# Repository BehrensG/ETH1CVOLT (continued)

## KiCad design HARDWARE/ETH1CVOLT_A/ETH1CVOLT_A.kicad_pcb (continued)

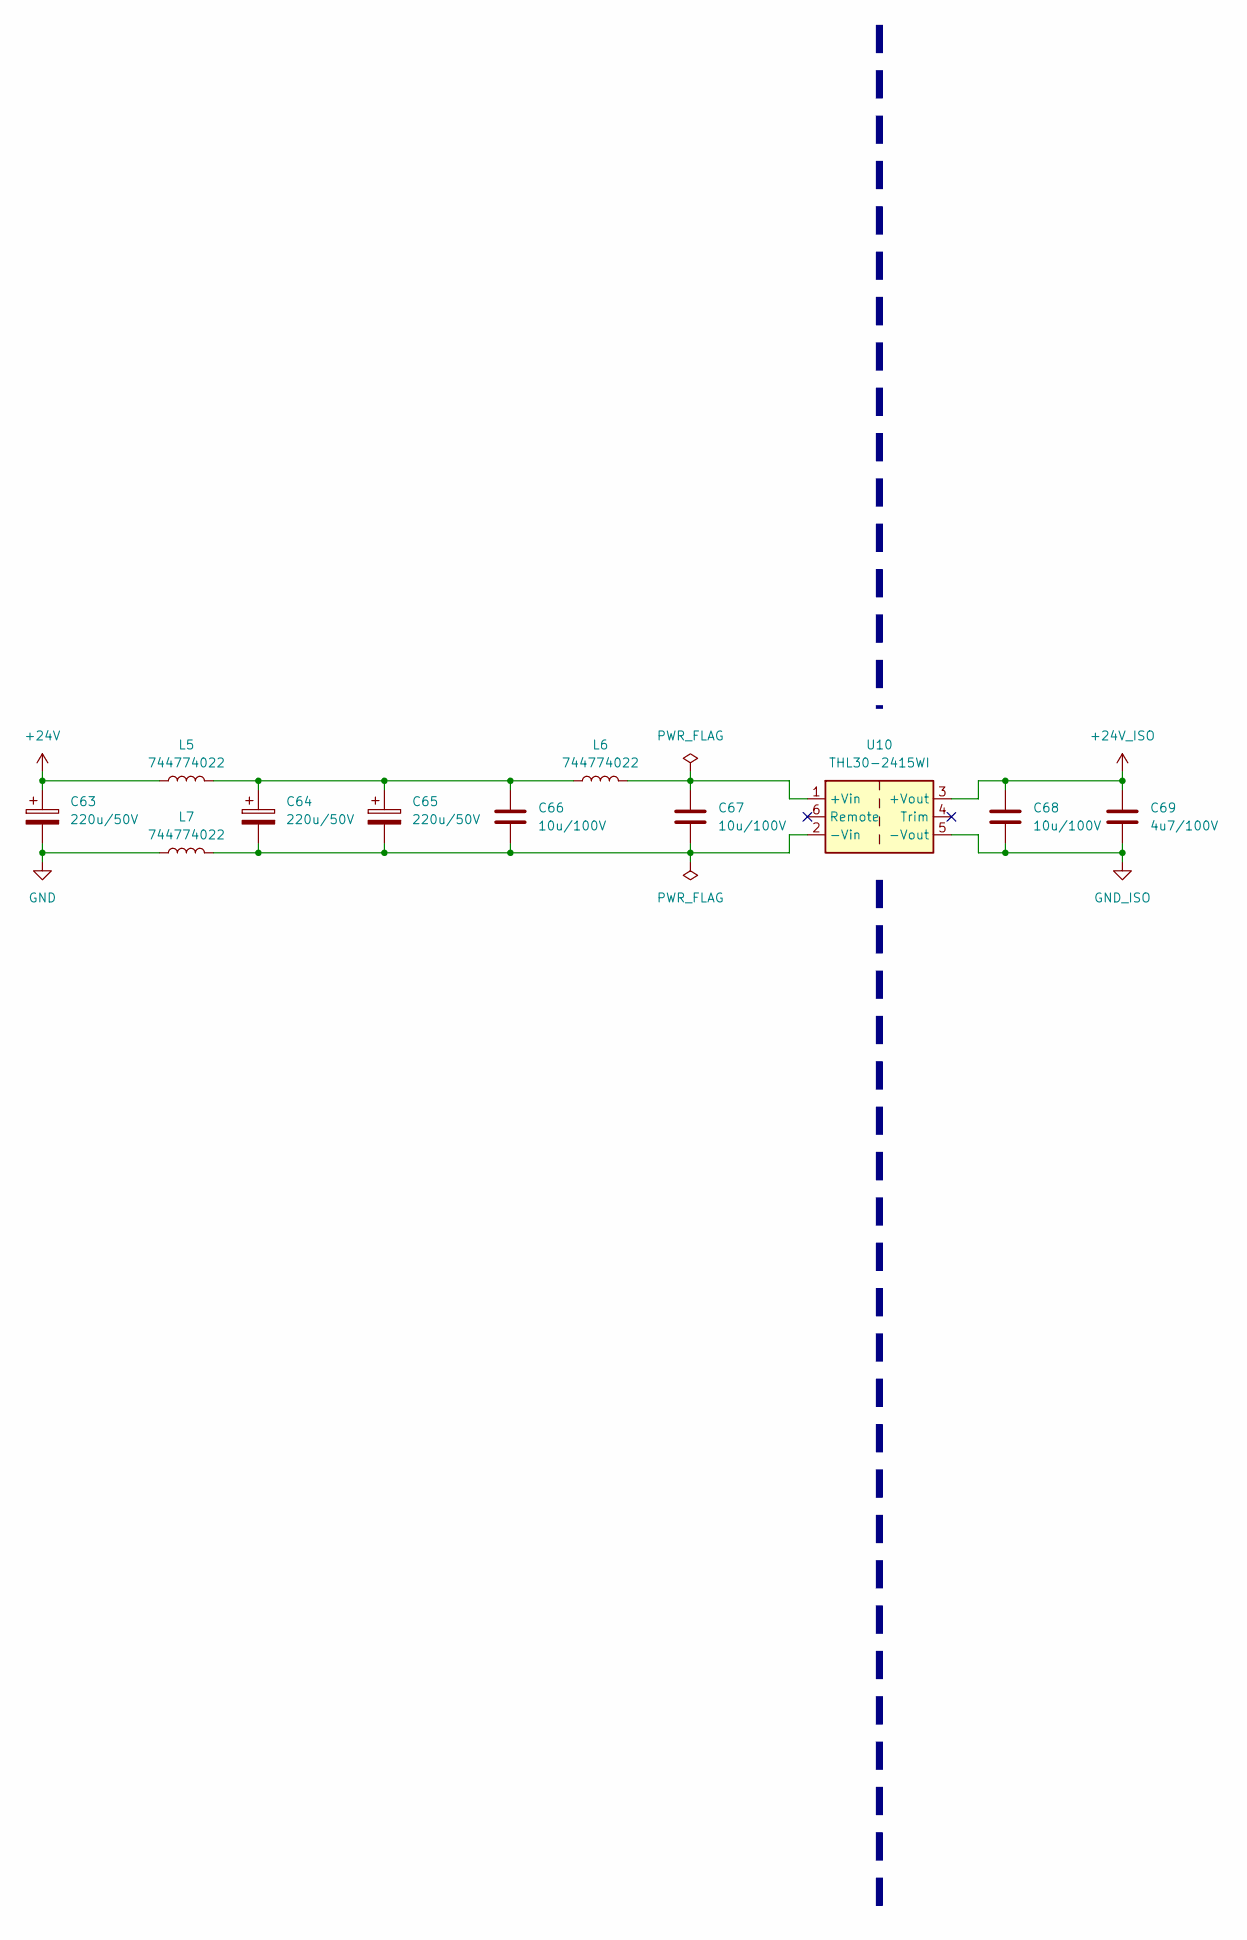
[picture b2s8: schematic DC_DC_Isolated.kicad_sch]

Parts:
C63, C64, C65: 220u/50V; CP_Elec_10x14.3
C66, C67, C68: 10u/100V; C_1210_3225Metric_Pad1.33x2.70mm_HandSolder
C69: 4u7/100V; C_1210_3225Metric_Pad1.33x2.70mm_HandSolder
L5, L6, L7: 744774022
U10: THL30-2415WI; Converter_DCDC_TRACO_THL30-xxxxWI_THT

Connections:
+24V: C63.1, L5.1; also elsewhere on the board
+24V_ISO: C68.1, C69.1, U10.3 (+Vout); also elsewhere on the board
GND: C63.2, L7.1; also elsewhere on the board
GND_ISO: C68.2, C69.2, U10.5 (-Vout); also elsewhere on the board
unnamed: C64.1, C65.1, C66.1, L5.2, L6.1
unnamed: C67.1, L6.2, U10.1 (+Vin)
unnamed: C64.2, C65.2, C66.2, C67.2, L7.2, U10.2 (-Vin)

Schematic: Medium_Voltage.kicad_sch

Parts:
C32, C39: 4p7; C_0603_1608Metric_Pad1.08x0.95mm_HandSolder
C33, C35, C40, C42: 4u7/100V; C_1210_3225Metric_Pad1.33x2.70mm_HandSolder
C34, C36, C41, C43: 10u/100V; C_1210_3225Metric_Pad1.33x2.70mm_HandSolder
C37, C44: 1u; C_0603_1608Metric_Pad1.08x0.95mm_HandSolder
C38: 1u/100V; C_0805_2012Metric_Pad1.18x1.45mm_HandSolder
D3, D4: PMEG6010EP,115; D_SOD-128
J4: 61030821821; PinSocket_2x04_P2.54mm_Vertical_SMD
L1: 74438335068
L2: 74489440068
R14, R19: 0; R_0603_1608Metric_Pad0.98x0.95mm_HandSolder
R15, R20: 499k; R_0805_2012Metric_Pad1.20x1.40mm_HandSolder
R16, R21: DNP; R_0603_1608Metric_Pad0.98x0.95mm_HandSolder; not fitted
R17: 18k7; R_0603_1608Metric_Pad0.98x0.95mm_HandSolder
R18: 100; R_0603_1608Metric_Pad0.98x0.95mm_HandSolder
R22: 10k; R_0603_1608Metric_Pad0.98x0.95mm_HandSolder
U5, U6: LT8330_S6; TSOT-23-6

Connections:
+24V_ISO: C33.1, C34.1, C40.1, C41.1, L1.1, L2.1, R14.1, R19.1, U5.6 (VIN), U6.6 (VIN); also elsewhere on the board
+44V_ISO: C32.1, C35.1, C36.1, D3.1 (K), J4.1, J4.2, R15.1
-41V_ISO: C39.1, C42.1, C43.1, J4.7, J4.8, L2.3, R20.1
GND_ISO: C33.2, C34.2, C35.2, C36.2, C37.1, C40.2, C41.2, C42.2, C43.2, C44.1, D4.1 (K), J4.3, J4.4, J4.5, J4.6, R16.2, R18.2, R21.2, R22.2, U5.2 (GND), U6.2 (GND); also elsewhere on the board
unnamed: D3.2 (A), L1.2, U5.1 (SW)
unnamed: C38.2, D4.2 (A), L2.2
unnamed: R17.2, R18.1
unnamed: R14.2, R16.1, U5.4 (EN/UVLO)
unnamed: C32.2, R15.2, R17.1, U5.3 (FBX)
unnamed: C37.2, U5.5 (INTVCC)
unnamed: R19.2, R21.1, U6.4 (EN/UVLO)
unnamed: C39.2, R20.2, R22.1, U6.3 (FBX)
unnamed: C44.2, U6.5 (INTVCC)
unnamed: C38.1, L2.4, U6.1 (SW)

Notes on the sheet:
-41V/55mA
+44V/55mA

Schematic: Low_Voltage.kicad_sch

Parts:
C45, C55: 1u/100V; C_0805_2012Metric_Pad1.18x1.45mm_HandSolder
C46, C58: 4p7; C_0603_1608Metric_Pad1.08x0.95mm_HandSolder
C47, C49, C52, C56, C59, C61, C71, C73, C75, C78, C81, C83, C85, C88: 4u7/100V; C_1210_3225Metric_Pad1.33x2.70mm_HandSolder
C48, C50, C53, C57, C60, C62, C72, C74, C76, C79, C82, C84, C86, C89: 10u/100V; C_1210_3225Metric_Pad1.33x2.70mm_HandSolder
C51, C70, C80, C90: 1u; C_0603_1608Metric_Pad1.08x0.95mm_HandSolder
C54: C; C_0603_1608Metric_Pad1.08x0.95mm_HandSolder
C77, C87: C; not fitted
D5, D6: PMEG6010EP,115; D_SOD-128
J5: 61030821821; PinSocket_2x04_P2.54mm_Vertical_SMD
L3, L4: 74489440068
L8, L9: 74408063470
R23, R33, R38, R42, R43: 0; R_0603_1608Metric_Pad0.98x0.95mm_HandSolder
R24, R34: 499k; R_0805_2012Metric_Pad1.20x1.40mm_HandSolder
R25, R35: DNP; R_0603_1608Metric_Pad0.98x0.95mm_HandSolder; not fitted
R26: 41k2; R_0603_1608Metric_Pad0.98x0.95mm_HandSolder
R27: 165k; R_0603_1608Metric_Pad0.98x0.95mm_HandSolder
R28, R31, R41: 10k; R_0603_1608Metric_Pad0.98x0.95mm_HandSolder
R29: 1k4; R_0603_1608Metric_Pad0.98x0.95mm_HandSolder
R30: 174k; R_0603_1608Metric_Pad0.98x0.95mm_HandSolder
R32: 2k4; R_0603_1608Metric_Pad0.98x0.95mm_HandSolder
R36: 19k6; R_0603_1608Metric_Pad0.98x0.95mm_HandSolder
R37: 220; R_0603_1608Metric_Pad0.98x0.95mm_HandSolder
R39: 68k; R_0603_1608Metric_Pad0.98x0.95mm_HandSolder
R40, R44: R; not fitted
R45: 10k; R_0603_1608Metric_Pad0.98x0.95mm_HandSolder; not fitted
U7, U9: LT8330_S6; TSOT-23-6
U8: TPS7A39; Texas_S-PVSON-N10_ThermalVias
U11, U13: ADP7142ARDZ-5.0; SOIC-8-1EP_3.9x4.9mm_P1.27mm_EP2.29x3mm
U12: MAX15062C; DFN-8_2x2mm_P0.5mm
U14: MAX15062B; DFN-8_2x2mm_P0.5mm

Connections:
+5VD_ISO: C83.1, C84.1, J5.6, L9.2, R43.1; also elsewhere on the board
+7V_ISO: C73.1, C74.1, C75.1, C76.1, C85.1, C86.1, J5.5, L8.2, R39.1, U11.5 (EN), U11.7 (VIN), U11.8 (VIN), U13.5 (EN), U13.7 (VIN), U13.8 (VIN)
+21V_ISO: C52.1, C53.1, J5.2, R27.1, U8.10 (OUTP)
+24V_ISO: C47.1, C48.1, C59.1, C60.1, C71.1, C72.1, C81.1, C82.1, J5.3, L3.1, L4.1, R23.1, R33.1, U7.6 (VIN), U9.6 (VIN), U12.1 (VIN), U12.2 (EN/UVLO), U14.1 (VIN), U14.2 (EN/UVLO); also elsewhere on the board
+VA_ISO: C78.1, C79.1, J5.7, R38.2, U11.1 (VOUT), U11.2 (VOUT)
+VD_ISO: C88.1, C89.1, J5.8, R42.2, U13.1 (VOUT), U13.2 (VOUT)
-21V_ISO: C56.2, C57.2, J5.1, R32.2, U8.6 (OUTN)
GND: D6.1 (K), L3.3; also elsewhere on the board
GND_ISO: C47.2, C48.2, C49.2, C50.2, C51.1, C52.2, C53.2, C54.2, C56.1, C57.1, C59.2, C60.2, C61.2, C62.2, C70.1, C71.2, C72.2, C73.2, C74.2, C75.2, C76.2, C77.2, C78.2, C79.2, C80.2, C81.2, C82.2, C83.2, C84.2, C85.2, C86.2, C87.2, C88.2, C89.2, C90.2, J5.4, R25.2, R26.1, R31.2, R35.2, R37.2, R40.2, R41.2, R44.2, R45.2, U7.2 (GND), U8.4 (GND), U8.11 (GND), U9.2 (GND), U11.4 (GND), U11.9 (GND), U12.7 (GND), U13.4 (GND), U13.9 (GND), U14.7 (GND); also elsewhere on the board
unnamed: C45.2, D5.2 (A), L3.2
unnamed: C46.1, C49.1, C50.1, D5.1 (K), R24.1, U8.1 (INP), U8.2 (EN)
unnamed: C55.2, D6.2 (A), L4.2
unnamed: R27.2, R29.1
unnamed: R30.2, R32.1
unnamed: R36.2, R37.1
unnamed: R23.2, R25.1, U7.4 (EN/UVLO)
unnamed: C46.2, R24.2, R26.2, U7.3 (FBX)
unnamed: C51.2, U7.5 (INTVCC)
unnamed: C45.1, L3.4, U7.1 (SW)
unnamed: R28.1, U8.8 (BUF)
unnamed: R28.2, R30.1, U8.7 (FBN)
unnamed: R29.2, R31.1, U8.9 (FBP)
unnamed: C58.1, C61.1, C62.1, L4.3, R34.1, U8.5 (INN)
unnamed: C54.1, U8.3 (NR/SS)
unnamed: R33.2, R35.1, U9.4 (EN/UVLO)
unnamed: C58.2, R34.2, R36.1, U9.3 (FBX)
unnamed: C70.2, U9.5 (INTVCC)
unnamed: C55.1, L4.4, U9.1 (SW)
unnamed: R38.1, R40.1, U11.3 (SENSE/ADJ)
unnamed: C77.1, U11.6 (SS)
unnamed: R39.2, R41.1, U12.4 (FB/Vout)
unnamed: L8.1, U12.8 (LX)
unnamed: C80.1, U12.3 (VCC)
unnamed: R42.1, R44.1, U13.3 (SENSE/ADJ)
unnamed: C87.1, U13.6 (SS)
unnamed: R43.2, R45.1, U14.4 (FB/Vout)
unnamed: L9.1, U14.8 (LX)
unnamed: C90.1, U14.3 (VCC)

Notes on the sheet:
+7V/300mA
+22V/100mA
+5V/300mA
+5V/200mA
-22V/100mA
+21V/100mA
-21V/100mA

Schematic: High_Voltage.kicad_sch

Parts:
C91, C92, C98, C103, C104, C110: 0.1u/200V; C_1210_3225Metric_Pad1.33x2.70mm_HandSolder
C93, C105: 4u7/100V; C_1210_3225Metric_Pad1.33x2.70mm_HandSolder
C94, C106: 10u/100V; C_1210_3225Metric_Pad1.33x2.70mm_HandSolder
C95, C99, C107, C111: 0.22u/200V; C_1210_3225Metric_Pad1.33x2.70mm_HandSolder
C96, C108: AEF08124R7M400R; CP_Elec_8x11.9
C97, C109: AEK0812100M250R; CP_Elec_8x11.9
C100, C112: 0.22u; C_0603_1608Metric_Pad1.08x0.95mm_HandSolder
C101, C113: 1u; C_0603_1608Metric_Pad1.08x0.95mm_HandSolder
C102, C114: 1n8; C_0603_1608Metric_Pad1.08x0.95mm_HandSolder
D7, D8, D10, D11, D13, D15, D16: DFLS1150; D_PowerDI-123
D9: 1N4148W; D_SOD-123
D14: DFLS1200; D_PowerDI-123
J9: 61031021821; PinSocket_2x05_P2.54mm_Vertical_SMD
K1: EE2-3NU; Relay_DPDT_Kemet_EE2_NU
L10, L11: 74437324100
R46, R60: 47/200V; R_0603_1608Metric_Pad0.98x0.95mm_HandSolder
R47, R48, R59, R61: 20/200V; R_0603_1608Metric_Pad0.98x0.95mm_HandSolder
R49, R51, R62, R63: 499k/100V; R_0805_2012Metric_Pad1.20x1.40mm_HandSolder
R50, R52: 10k/2W; R_2512_6332Metric_Pad1.40x3.35mm_HandSolder
R53, R64: 0; R_0603_1608Metric_Pad0.98x0.95mm_HandSolder
R54, R65: DNP; R_0603_1608Metric_Pad0.98x0.95mm_HandSolder; not fitted
R55: 14k7; R_0603_1608Metric_Pad0.98x0.95mm_HandSolder
R56, R66: 44k2; R_0603_1608Metric_Pad0.98x0.95mm_HandSolder
R57, R68: 107k; R_0603_1608Metric_Pad0.98x0.95mm_HandSolder
R67: 7k32; R_0603_1608Metric_Pad0.98x0.95mm_HandSolder
U15, U17: LT8365; 05-08-1871_ADI

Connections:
+3.3V: D9.1 (K), K1.1; also elsewhere on the board
+24V_ISO: C93.1, C94.1, C105.1, C106.1, L10.1, L11.1, R53.1, R64.1, U15.3 (VIN), U17.3 (VIN); also elsewhere on the board
+110V_ISO: C96.1, C97.1, C98.1, J9.1, J9.2, K1.4, R46.2, R49.1
-110V_ISO: C108.2, C109.2, C110.2, J9.9, J9.10, K1.9, R60.2, R62.1
/Block Diagram/Power/Power Isolated/High Voltage/+HV1: C91.1, L10.2, U15.14 (SW2), U15.16 (SW1)
/Block Diagram/Power/Power Isolated/High Voltage/+HV2: C91.2, C92.1, D10.2 (A), D11.1 (K)
/Block Diagram/Power/Power Isolated/High Voltage/+HV3: C92.2, D7.2 (A), D8.1 (K)
/Block Diagram/Power/Power Isolated/High Voltage/+HV4: C95.1, D7.1 (K), R46.1
/Block Diagram/Power/Power Isolated/High Voltage/-HV1: C103.1, L11.2, U17.14 (SW2), U17.16 (SW1)
/Block Diagram/Power/Power Isolated/High Voltage/-HV2: C103.2, C104.1, D15.1 (K), D16.2 (A)
/Block Diagram/Power/Power Isolated/High Voltage/-HV3: C104.2, D13.1 (K), D14.2 (A)
/Block Diagram/Power/Power Isolated/High Voltage/-HV4: C107.1, R59.2, R60.1
GND: C110.1, C111.2, D9.2 (A), D16.1 (K), K1.12; also elsewhere on the board
GND_ISO: C93.2, C94.2, C96.2, C97.2, C98.2, C99.2, C100.2, C101.2, C102.2, C105.2, C106.2, C108.1, C109.1, C112.2, C113.2, C114.2, J9.5, J9.6, R48.2, R50.2, R52.2, R54.2, R55.2, R57.2, R65.2, R67.2, R68.2, U15.7 (BIAS), U15.12 (SYNC/MODE), U15.17 (GND), U17.7 (BIAS), U17.12 (SYNC/MODE), U17.17 (GND); also elsewhere on the board
unnamed: C102.1, R56.2
unnamed: C114.1, R66.2
unnamed: D8.2 (A), R47.1
unnamed: C95.2, C99.1, D10.1 (K), R47.2
unnamed: D11.2 (A), R48.1
unnamed: D13.2 (A), R59.1
unnamed: C107.2, C111.1, D14.1 (K), R61.2
unnamed: D15.2 (A), R61.1
unnamed: K1.3, R50.1
unnamed: K1.10, R52.1
unnamed: R49.2, R51.1
unnamed: R62.2, R63.1
unnamed: R53.2, R54.1, U15.1 (EN/UVLO)
unnamed: R51.2, R55.1, U15.9 (FBX)
unnamed: C101.1, U15.5 (INVTCC)
unnamed: R57.1, U15.10 (RT)
unnamed: C100.1, U15.11 (SS)
unnamed: R56.1, U15.8 (VC)
unnamed: R64.2, R65.1, U17.1 (EN/UVLO)
unnamed: R63.2, R67.1, U17.9 (FBX)
unnamed: C113.1, U17.5 (INVTCC)
unnamed: R68.1, U17.10 (RT)
unnamed: C112.1, U17.11 (SS)
unnamed: R66.1, U17.8 (VC)

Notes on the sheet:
+110V/15mA
400kHz, 10V to 30V Input, -110V Output, Low Output Ripple, HV Supply
Connector
-110V/15mA
400kHz, 10V to 30V Input, 110V Output, Low Output Ripple, HV Supply
All resistors have 1% tolerance. Power 0.1 - 0.25 W All MLCCs capacitors are X7R
Discharge

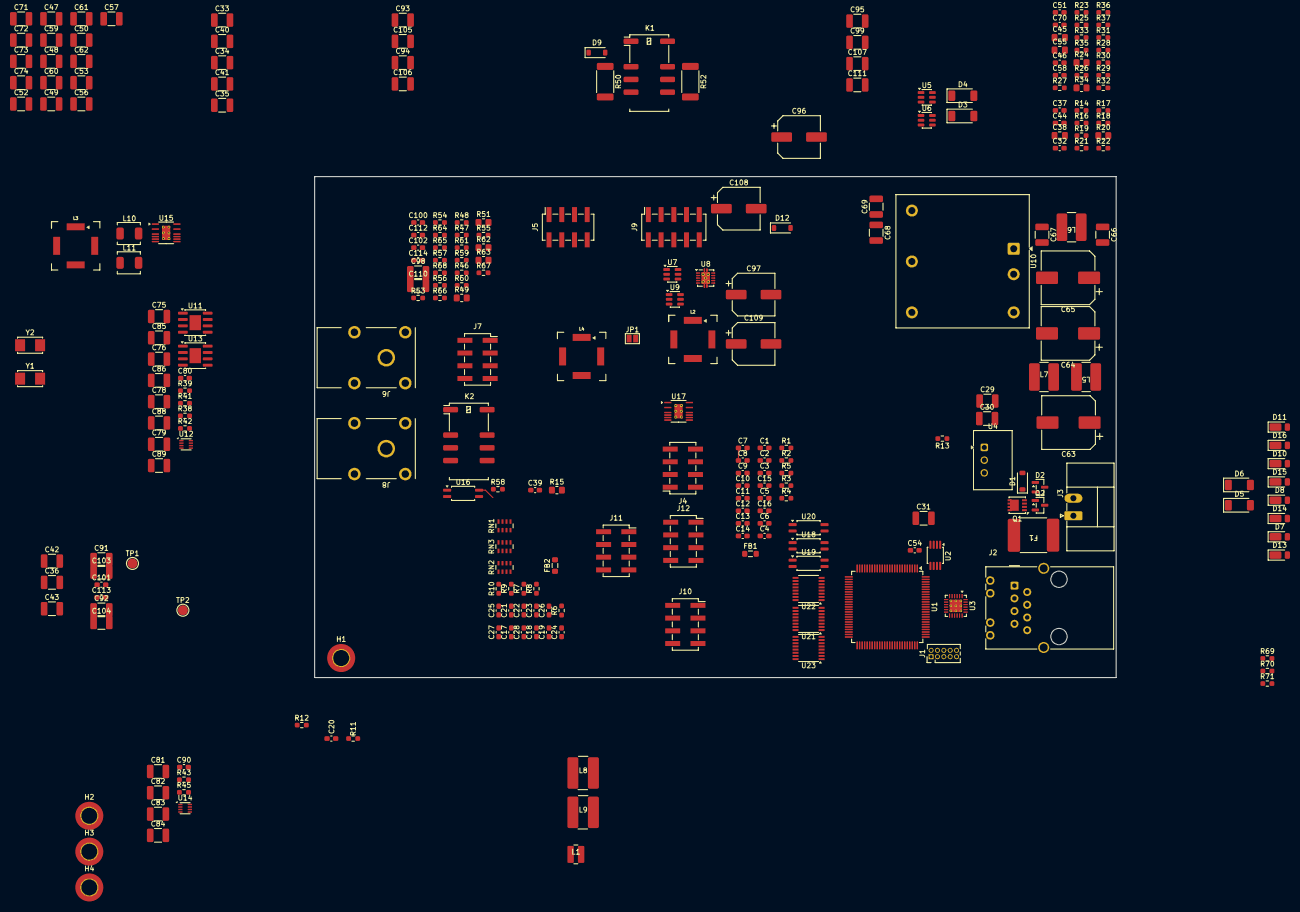
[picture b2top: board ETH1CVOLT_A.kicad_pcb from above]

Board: 2 copper layers, 160.0 x 100.0 mm, 262 parts (0 on the bottom side), 183 nets.

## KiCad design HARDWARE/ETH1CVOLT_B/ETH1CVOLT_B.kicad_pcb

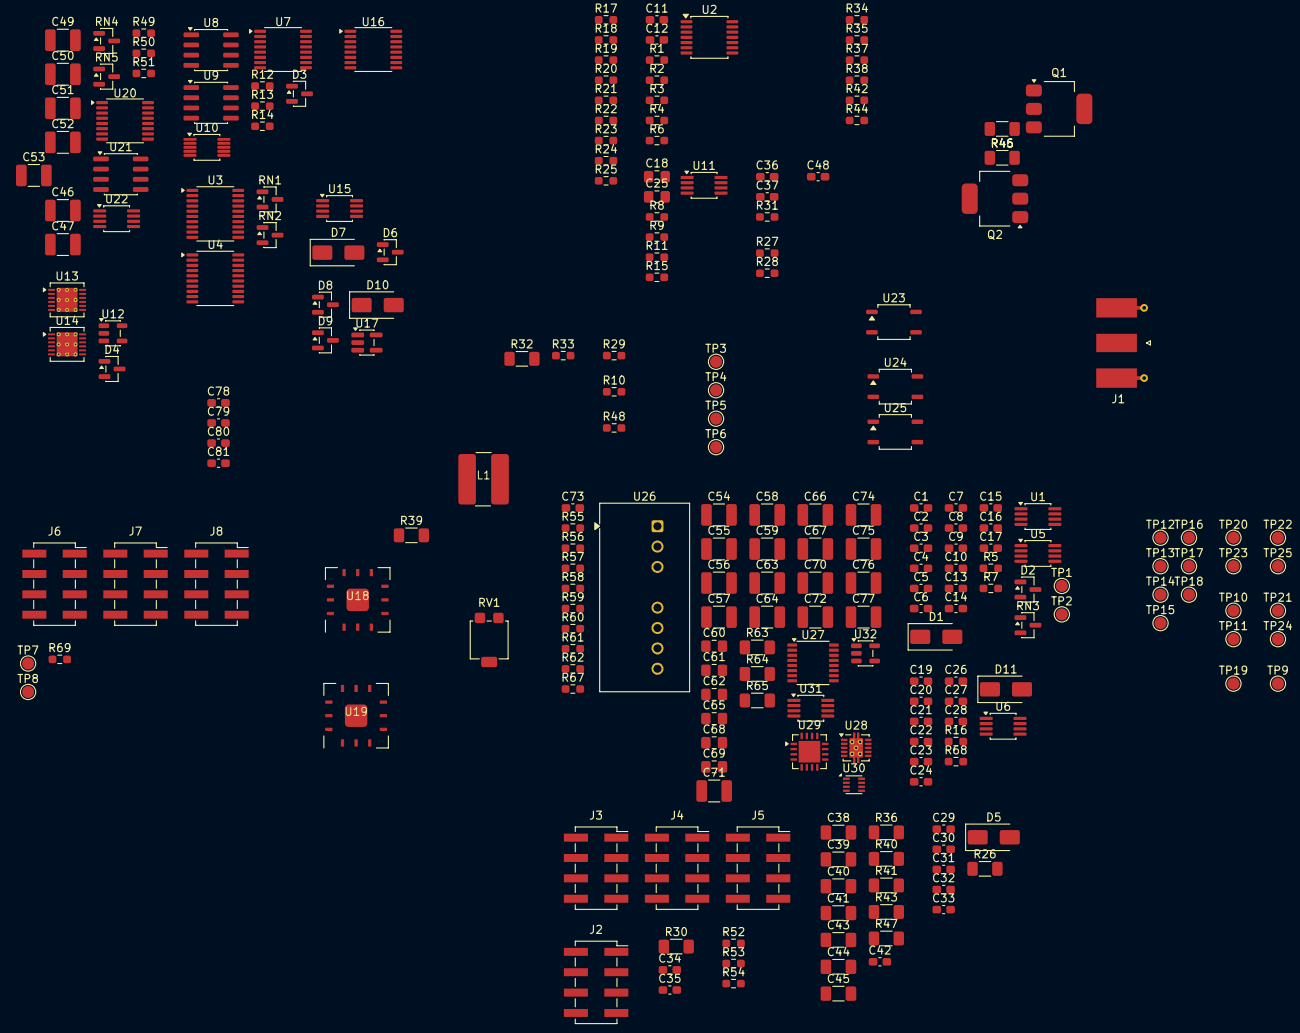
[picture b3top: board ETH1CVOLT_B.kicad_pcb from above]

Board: 2 copper layers, 234 parts (0 on the bottom side), 134 nets, no tracks yet.

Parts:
C1, C2, C3, C4, C5, C6, C7, C8, C9, C10, C13, C14, C15, C16, C17, C19, C20, C21, C22, C23, C24, C26, C27, C28, C29, C30, C31, C32, C33, C34, C35, C36, C37, C42, C78, C81: 0.1u/100V; C_0603_1608Metric_Pad1.08x0.95mm_HandSolder
C11, C12: 470p/100V; C_0603_1608Metric_Pad1.08x0.95mm_HandSolder
C18, C25: 6u8/16V; C_0805_2012Metric_Pad1.18x1.45mm_HandSolder
C38, C39, C40, C41: 0.1u/250V; C_1206_3216Metric_Pad1.33x1.80mm_HandSolder
C43, C44: C/250V; C_1206_3216Metric_Pad1.33x1.80mm_HandSolder
C45: C/200V; C_1206_3216Metric_Pad1.33x1.80mm_HandSolder
C46, C49, C51: 4u7/100V; C_1210_3225Metric_Pad1.33x2.70mm_HandSolder
C47, C50, C52, C53, C71: 10u/100V; C_1210_3225Metric_Pad1.33x2.70mm_HandSolder
C48, C73, C79, C80: 1u/50V; C_0603_1608Metric_Pad1.08x0.95mm_HandSolder
C54, C56, C57, C63, C64, C70, C74, C76: 4u7/50V; C_1210_3225Metric_Pad1.33x2.70mm_HandSolder
C55, C58, C59, C66, C67, C72, C75, C77: 10u/50V; C_1210_3225Metric_Pad1.33x2.70mm_HandSolder
C60: C/50V; C_0805_2012Metric_Pad1.18x1.45mm_HandSolder
C61, C65, C69: 1u/50V; C_0805_2012Metric_Pad1.18x1.45mm_HandSolder
C62, C68: 10u/16V; C_0805_2012Metric_Pad1.18x1.45mm_HandSolder
D1, D11: SMAJ14CA; D_SMA
D2, D3, D4, D6, D8, D9: BAV199; SOT-23
D5: SMAJ43CA; D_SMA
D7: SMAJ26CA; D_SMA
D10: SMAJ120CA; D_SMA
J1: 73251-1153; SMA_Molex_73251-1153_EdgeMount_Horizontal
J2: Conn_02x04_Odd_Even; PinSocket_2x04_P2.54mm_Vertical_SMD
J3, J4, J5, J6, J7, J8: 61000821121; PinSocket_2x04_P2.54mm_Vertical_SMD
L1: 74408063470
Q1: PBHV8140Z,115; SOT-223-3_TabPin2
Q2: PBHV9540Z,115; SOT-223-3_TabPin2
R1, R10, R16, R18, R31, R48: 100k/0.1%; R_0603_1608Metric_Pad0.98x0.95mm_HandSolder
R2, R3, R4, R5, R6, R7: 10k/0.1%; R_0603_1608Metric_Pad0.98x0.95mm_HandSolder
R8, R9: 0R; R_0603_1608Metric_Pad0.98x0.95mm_HandSolder
R11, R15, R59, R68, R69: 100; R_0603_1608Metric_Pad0.98x0.95mm_HandSolder
R12, R49: 180k/0.05%; R_0603_1608Metric_Pad0.98x0.95mm_HandSolder
R13, R50: 18k/0.05%; R_0603_1608Metric_Pad0.98x0.95mm_HandSolder
R14, R51: 2k/0.05%; R_0603_1608Metric_Pad0.98x0.95mm_HandSolder
R17, R23: 10k/0.1%/250mW; R_0603_1608Metric_Pad0.98x0.95mm_HandSolder
R19: 147k/0.1%; R_0603_1608Metric_Pad0.98x0.95mm_HandSolder
R20: 2k7/0.1%; R_0603_1608Metric_Pad0.98x0.95mm_HandSolder
R21, R27, R28, R34: 49k9/0.1%; R_0603_1608Metric_Pad0.98x0.95mm_HandSolder
R22, R24: 536k; R_0603_1608Metric_Pad0.98x0.95mm_HandSolder
R25, R29, R52, R53, R54: 1k/0.1%; R_0603_1608Metric_Pad0.98x0.95mm_HandSolder
R26, R30, R47: 100/2W; R_1206_3216Metric_Pad1.30x1.75mm_HandSolder
R32: RQ73C2B499KBTD; R_1206_3216Metric_Pad1.30x1.75mm_HandSolder
R33: RN73C1J100RBTDF; R_0603_1608Metric_Pad0.98x0.95mm_HandSolder
R35: 9k76/0.1%; R_0603_1608Metric_Pad0.98x0.95mm_HandSolder
R36, R41: R/200V; R_1206_3216Metric_Pad1.30x1.75mm_HandSolder
R37, R38, R67: 0; R_0603_1608Metric_Pad0.98x0.95mm_HandSolder
R39: TNPW120639K2BEEN; R_1206_3216Metric_Pad1.30x1.75mm_HandSolder
R40, R63, R64: 0/200V; R_1206_3216Metric_Pad1.30x1.75mm_HandSolder
R42, R44: 500; R_0603_1608Metric_Pad0.98x0.95mm_HandSolder
R43: 1k/250mW/200V; R_1206_3216Metric_Pad1.30x1.75mm_HandSolder
R45, R46: 5/250mW/200V; R_1206_3216Metric_Pad1.30x1.75mm_HandSolder
R55, R58, R61: 10k; R_0603_1608Metric_Pad0.98x0.95mm_HandSolder
R56: 118k; R_0603_1608Metric_Pad0.98x0.95mm_HandSolder
R57: 107k; R_0603_1608Metric_Pad0.98x0.95mm_HandSolder
R60: 68k; R_0603_1608Metric_Pad0.98x0.95mm_HandSolder
R62: 499/0.1%; R_0603_1608Metric_Pad0.98x0.95mm_HandSolder
R65: RT1206BRD071RL; R_1206_3216Metric_Pad1.30x1.75mm_HandSolder
RN1, RN2, RN3, RN4, RN5: MPMT1002AT5; SOT-23
RV1: R_Potentiometer_Trim; Potentiometer_Bourns_3314G_Vertical
TP1, TP2, TP3, TP4, TP5, TP6, TP7, TP8, TP9, TP10, TP11, TP12, TP13, TP14, TP15, TP16, TP17, TP18, TP19, TP20, TP21, TP22, TP23, TP24, TP25: TestPoint; TestPoint_Pad_D1.5mm
U1, U6: ADG5419BRMZ-RL7; MSOP-8_3x3mm_P0.65mm
U2: ADA4522-4ARUZ; TSSOP-14_4.4x5mm_P0.65mm
U3, U4: DAC81401PWR; TSSOP-20_4.4x6.5mm_P0.65mm
U5, U11, U15: ADA4522-1ARMZ; MSOP-8_3x3mm_P0.65mm
U7: DG412LEDQ; TSSOP-16_4.4x5mm_P0.65mm
U8: LTC2400; SOIC-8_3.9x4.9mm_P1.27mm
U9: LT1077S8#TRPBF; SOIC-8_3.9x4.9mm_P1.27mm
U10: AD8475xRMZ; MSOP-10_3x3mm_P0.5mm
U12: SN74LVC1G125DBV; SOT-23-5
U13, U14: OPA593; WSON-12-1EP_4x4mm_P0.5mm_EP2.6x3mm_ThermalVias
U16: TMUX8109PWR; TSSOP-16_4.4x5mm_P0.65mm
U17: 74LV1T08GV; SC-74A-5_1.55x2.9mm_P0.95mm
U18, U19: ADHV4702-1; CP-12-8
U20: DG412EUE+; TSSOP-16_4.4x5mm_P0.65mm
U21: LT1027CCS8-5#PBF; SOIC-8_3.9x4.9mm_P1.27mm
U22: ADA4077-1xRM; MSOP-8_3x3mm_P0.65mm
U23, U24, U25: CPC1010N; SOP-4_3.8x4.1mm_P2.54mm
U26: TEC3-2423UI; Converter_DCDC_TRACO_TEC3-24xxUI_THT
U27: ISO7761FDBQ; SSOP-16_3.9x4.9mm_P0.635mm
U28: TPS7A39; Texas_S-PVSON-N10_ThermalVias
U29: ADS8681RUM; QFN-16-1EP_4x4mm_P0.65mm_EP2.7x2.7mm
U30: MAX15062C; DFN-8_2x2mm_P0.5mm
U31: AD8221ARM; MSOP-8_3x3mm_P0.65mm
U32: ADP7142AUJZ-5.0; TSOT-23-5

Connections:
+2.5VREF_ISO: C27.1, C51.1, C52.1, RN4.3, U10.4 (VOCM)
+5V: C61.1, C76.1, C77.1, R67.2, TP13.1, U27.16 (Vcc2), U29.7 (~RST), U29.14 (DVDD), U29.16 (AVDD), U32.5 (VOUT)
+5VD_ISO: R52.1, R53.1, R54.1
+5VREF_ISO: C28.1, C49.1, C50.1, C78.2, C79.2, C80.2, C81.2, RN4.2, RV1.3, U3.1 (VREFIO), U4.1 (VREFIO), U8.2 (VREF), U21.4 (VOUT), U22.3 (+)
+7V_ISO: C46.1, C47.1, U21.8 (VIN)
+14V: C63.1, C66.1, R57.1, TP15.1, U28.10 (OUTP), U31.8 (Vs+)
+15V: C56.1, C58.1, C70.1, C72.1, TP17.1, U26.6 (+Vout), U28.1 (INP), U28.2 (EN), U30.1 (VIN), U30.2 (EN/UVLO)
+21V_ISO: C2.1, C4.1, C6.1, C8.1, C10.1, C19.1, C26.1, C34.1, C36.1, D2.2 (A), D6.2 (A), U1.4 (V+), U2.4 (V+), U3.5 (AVDD), U4.5 (AVDD), U5.7 (V+), U6.4 (V+), U11.7 (V+), U15.7 (V+), U16.14 (VDD), U20.13 (V+), U22.7 (V+)
+24V_ISO: C54.1, C55.1, U26.2 (+Vin)
+44V_ISO: C29.1, C30.1, D4.2 (A), U13.10 (V+), U14.10 (V+)
+110V_ISO: C38.1, C39.1, Q1.2 (C), U18.7 (VCC), U19.7 (VCC)
+VA_ISO: C13.1, C15.1, C21.1, C22.1, C23.1, C24.1, D3.2 (A), U3.20 (VDD), U4.20 (VDD), U7.13 (V+), U8.1 (VCC), U9.7 (V+), U10.3 (+Vs)
+VD_ISO: C14.1, C16.1, C17.1, C33.1, C42.1, R8.1, R10.1, R48.1, U1.5 (VL), U3.17 (IOVDD), U4.17 (IOVDD), U6.5 (VL), U7.12 (VL), U12.5 (VCC), U16.2 (EN), U17.5 (VCC), U20.12 (VL), U27.1 (Vcc1)
-14V: C64.2, C67.2, R56.2, TP16.1, U28.6 (OUTN), U31.5 (Vs-)
-15V: C57.2, C59.2, TP18.1, U26.8 (-Vout), U28.5 (INN)
-21V_ISO: C1.1, C3.1, C5.1, C7.1, C9.1, C20.1, C35.1, C37.1, D2.1 (K), D6.1 (K), U1.7 (V-), U2.11 (V-), U3.3 (AVSS), U4.3 (AVSS), U5.4 (V-), U6.7 (V-), U11.4 (V-), U15.4 (V-), U16.3 (VSS)
-41V_ISO: C31.1, C32.1, D4.1 (K), R22.1, R24.1, U13.6 (V-), U13.13 (EPAD), U14.6 (V-), U14.13 (EPAD)
-110V_ISO: C40.1, C41.1, Q2.2 (C), U18.4 (VEE), U19.4 (VEE)
/Block Diagram/ADC/ADC_MEAS: U6.2, U16.9 (DB)
/Block Diagram/ADC/AUX_SEL: U1.6, U6.6
/Block Diagram/ADC/SEL_x1: U7.1, U20.1
/Block Diagram/ADC/SEL_x10: U7.8, U20.8
/Block Diagram/ADC/SEL_x100: U7.9, U20.9
/Block Diagram/Connectors Input/DAC_SCLK: U3.14 (SCLK), U4.14 (SCLK)
/Block Diagram/Connectors Input/DAC_~SYNC: U3.16 (~SYNC), U4.16 (~SYNC)
/Block Diagram/Connectors Output/OUT+: J2.1, J2.2, R63.2, R65.1
/Block Diagram/Current Measurement/CURR_P_MEAS: R64.2, R65.2, TP19.1, U23.3, U24.3, U25.3
/Block Diagram/Current Measurement/CURR_SCLK_ISO: U27.14 (OUTB), U29.10 (SCLK)
/Block Diagram/Current Measurement/CURR_SDI_ISO: U27.13 (OUTC), U29.8 (SDI)
/Block Diagram/Current Measurement/CURR_SDO_ISO: U27.10 (INF), U29.11 (SDO-0)
/Block Diagram/Current Measurement/CURR_~CS_ISO: U27.15 (OUTA), U29.9 (CONVST/~CS)
/Block Diagram/DAC/DAC_OUTPUT: U1.1, U16.8 (DA)
/Block Diagram/DAC/VOUT_A: C11.2, R2.1, RN1.2, U2.10 (+), U3.9 (VOUT)
/Block Diagram/DAC/VOUT_B: C12.2, R1.1, U2.12 (+), U4.9 (VOUT)
/Block Diagram/HV Output/HV_DAC: D8.2 (A), D9.1 (K), U16.7 (S4A), U18.2 (IN+)
/Block Diagram/HV Output/HV_ENABLE: U17.4 (Y), U18.8 (~SD), U19.8 (~SD)
/Block Diagram/HV Output/HV_MEAS: R33.2, R34.1, TP24.1, U16.11 (S3B)
/Block Diagram/HV Output/HV_OUTPUT: D10.2 (A2), R47.2, TP21.1, U25.4
/Block Diagram/LV Output/LV_DAC: R29.2, R30.1, U16.4 (S1A)
/Block Diagram/LV Output/LV_MEAS: R27.2, R28.1, TP23.1, U16.13 (S1B)
/Block Diagram/LV Output/LV_OUTPUT: D6.3 (K), D7.2 (A2), R30.2, TP20.1, U23.4
/Block Diagram/MUX/MUX_A0: U12.2, U16.1 (A0), U17.2 (A)
/Block Diagram/MUX/MUX_A1: U16.16 (A1), U17.1 (B)
/Block Diagram/MUX/MV_DAC: R18.2, U13.4 (+IN), U16.5 (S2A)
/Block Diagram/MUX/MV_MEAS: R20.2, R21.1, TP25.1, U16.12 (S2B)
/Block Diagram/MUX/VREF_TEST: U16.10 (S4B), U20.3, U20.7, U20.11
/Block Diagram/MV Output/MV_ENABLE: U12.4, U13.12 (E/D), U14.12 (E/D)
/Block Diagram/MV Output/MV_OUTPUT: D4.3 (K), D5.2 (A2), R26.2, TP22.1, U24.4
GNDS: C56.2, C57.1, C58.2, C59.1, C60.1, C61.2, C62.2, C63.2, C64.1, C65.2, C66.2, C67.1, C68.2, C69.2, C70.2, C71.2, C72.2, C73.2, C74.2, C75.2, C76.2, C77.2, R58.2, R61.2, TP14.1, U26.7 (Com), U27.9 (GND2), U28.4 (GND), U28.11 (GND), U29.1 (AGND), U29.3 (REFGND), U29.6 (AIN_GND), U29.15 (DGND), U29.17 (PAD), U30.7 (GND), U31.6 (Ref), U32.2 (GND)
GND_ISO: C1.2, C2.2, C3.2, C4.2, C5.2, C6.2, C7.2, C8.2, C9.2, C10.2, C13.2, C14.2, C15.2, C16.2, C17.2, C18.2, C19.2, C20.2, C21.2, C22.2, C23.2, C24.2, C25.1, C26.2, C27.2, C28.2, C29.2, C30.2, C31.2, C32.2, C33.2, C34.2, C35.2, C36.2, C37.2, C38.2, C39.2, C40.2, C41.2, C42.2, C46.2, C47.2, C48.2, C49.2, C50.2, C51.2, C52.2, C53.2, C54.2, C55.2, C78.1, C79.1, C80.1, C81.1, D1.1 (A1), D3.1 (K), D5.1 (A1), D7.1 (A1), D10.1 (A1), D11.1 (A1), J1.2 (Ext), J2.7, J2.8, R5.2, R9.2, R14.2, R16.1, R17.1, R18.1, R21.2, R28.2, R31.2, R34.2, R35.1, R37.1, R38.1, R51.2, RN3.1, RN4.1, RN5.2, RV1.1, U1.3 (GND), U2.3 (+), U2.5 (+), U3.2 (VREFGND), U3.11 (VSENSEN), U3.19 (GND), U4.2 (VREFGND), U4.11 (VSENSEN), U4.19 (GND), U5.2 (-), U6.3 (GND), U7.4 (V-), U7.5 (GND), U8.4 (GND), U9.4 (V-), U10.2 (-IN0.4x), U10.8 (-Vs), U12.1, U12.3 (GND), U13.1 (E/D_Com), U14.1 (E/D_Com), U16.15 (GND), U17.3 (GND), U18.10 (DGND), U18.13 (EPAD), U19.10 (DGND), U19.13 (EPAD), U20.4 (V-), U20.5 (GND), U21.2 (GND), U22.4 (V-), U26.1 (-Vin), U27.8 (GND1)
unnamed: C25.2, R15.1, TP4.1
unnamed: C43.2, R36.1
unnamed: C44.2, R41.1
unnamed: C45.2, R39.2, R40.2, R43.2, R45.2, R46.1, R47.1
unnamed: C53.1, R49.1, RN5.1, U20.2, U22.6
unnamed: D1.2 (A2), D2.3 (K), R69.2, U5.3 (+)
unnamed: D3.3 (K), R11.2, R12.1, TP10.1, U7.3, U9.6
unnamed: C45.1, D8.1 (K), D9.2 (A), R35.2, R39.1, U18.12 (IN-)
unnamed: D11.2 (A2), R68.1, TP5.1, U10.9 (+IN0.4x)
unnamed: J1.1 (In), R69.1
unnamed: Q1.1 (B), R42.2
unnamed: Q1.3 (E), R45.1
unnamed: Q2.1 (B), R44.2
unnamed: Q2.3 (E), R46.2
unnamed: R3.2, R4.1, RN1.1, RN2.2, U2.1
unnamed: R5.1, R7.2, RN3.3
unnamed: R6.2, RN2.1, TP8.1, U1.2, U2.7
unnamed: R7.1, RN3.2, TP7.1, U1.8, U5.6
unnamed: R10.2, U7.16
unnamed: R12.2, R13.1, U7.7
unnamed: R13.2, R14.1, U7.11
unnamed: R16.2, U6.8
unnamed: R19.2, R20.1
unnamed: R32.2, R33.1
unnamed: R48.2, U20.16
unnamed: R49.2, R50.1, U20.6
unnamed: R50.2, R51.1, U20.10
unnamed: R52.2, U23.1
unnamed: R53.2, U24.1
unnamed: R54.2, U25.1
unnamed: R59.2, U31.7
unnamed: R62.1, U31.2 (Rg)
unnamed: R62.2, U31.3 (Rg)
unnamed: R1.2, R2.2, R3.1, RN1.3, TP9.1, U2.2 (-)
unnamed: R4.2, R6.1, RN2.3, U2.6 (-)
unnamed: U2.8, U2.9 (-), U3.10 (VSENSEP)
unnamed: U2.13 (-), U2.14, U4.10 (VSENSEP)
unnamed: C11.1, U3.7 (CCOMP)
unnamed: U3.15 (SDIN), U4.13 (SDO)
unnamed: TP1.1, U3.12 (~FAULT)
unnamed: C12.1, U4.7 (CCOMP)
unnamed: TP2.1, U4.12 (~FAULT)
unnamed: U7.14, U7.15
unnamed: R8.2, R9.1, U8.8 (Fo)
unnamed: C18.1, R11.1, TP3.1, U8.3 (VIN)
unnamed: U7.2, U7.6, U7.10, U9.2 (-)
unnamed: TP11.1, U9.3 (+), U10.5 (+)
unnamed: R15.2, U10.6 (-)
unnamed: TP6.1, U6.1, U11.3 (+)
unnamed: R68.2, U11.2 (-), U11.6
unnamed: R17.2, R23.1, U13.3 (-IN)
unnamed: R24.2, U13.11 (ILIMIT)
unnamed: R23.2, R25.2, R26.1, U13.9 (OUT)
unnamed: R25.1, U14.4 (+IN)
unnamed: R19.1, U14.3 (-IN), U14.9 (OUT)
unnamed: R22.2, U14.11 (ILIMIT)
unnamed: R29.1, U15.3 (+)
unnamed: R27.1, U15.2 (-), U15.6
unnamed: R31.1, U16.6 (S3A)
unnamed: C44.1, U18.11 (COMP)
unnamed: R41.2, R42.1, R43.1, R44.1, U18.6 (OUT)
unnamed: R37.2, U18.9 (RADJ)
unnamed: C43.1, U19.11 (COMP)
unnamed: R40.1, U19.2 (IN+)
unnamed: R32.1, R36.2, U19.6 (OUT), U19.12 (IN-)
unnamed: R38.2, U19.9 (RADJ)
unnamed: U20.14, U20.15
unnamed: C48.1, U21.1 (NR)
unnamed: RV1.2, U21.3 (VTRIM)
unnamed: RN5.3, U22.2 (-)
unnamed: R55.1, U28.8 (BUF)
unnamed: R55.2, R56.1, U28.7 (FBN)
unnamed: R57.2, R58.1, U28.9 (FBP)
unnamed: C60.2, U28.3 (NR/SS)
unnamed: C71.1, R59.1, TP12.1, U29.5 (AIN_P)
unnamed: C68.1, C69.1, U29.4 (REFCAP)
unnamed: C62.1, C65.1, U29.2 (REFIO)
unnamed: R60.2, R61.1, U30.4 (FB/Vout)
unnamed: L1.1, U30.8 (LX)
unnamed: C73.1, U30.3 (VCC)
unnamed: R64.1, U31.4 (+)
unnamed: R63.1, U31.1 (-)
unnamed: C74.1, C75.1, L1.2, R60.1, U32.1 (VIN), U32.3 (EN)
unnamed: R67.1, U32.4 (SENSE/ADJ)

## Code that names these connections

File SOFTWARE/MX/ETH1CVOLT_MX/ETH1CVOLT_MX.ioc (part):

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Mcu.Name=STM32H743VITx
Mcu.Package=LQFP100
Mcu.UserName=STM32H743VITx
PA1.GPIOParameters=GPIO_Speed_Default_HIGH
PA1.GPIO_Speed_Default_HIGH=GPIO_SPEED_FREQ_VERY_HIGH
PA1.Mode=RMII
PA1.Signal=ETH_REF_CLK
PA13\ (JTMS/SWDIO).Mode=Serial_Wire
PA13\ (JTMS/SWDIO).Signal=DEBUG_JTMS-SWDIO
PA14\ (JTCK/SWCLK).Mode=Serial_Wire
PA14\ (JTCK/SWCLK).Signal=DEBUG_JTCK-SWCLK
PA15\ (JTDI).GPIOParameters=GPIO_Label
PA15\ (JTDI).GPIO_Label=MCU_DAC_nCS
PA15\ (JTDI).Mode=NSS_Signal_Hard_Output
PA15\ (JTDI).Signal=SPI3_NSS
PA2.GPIOParameters=GPIO_Speed_Default_HIGH
PA2.GPIO_Speed_Default_HIGH=GPIO_SPEED_FREQ_VERY_HIGH
PA2.Mode=RMII
PA2.Signal=ETH_MDIO
PA4.GPIOParameters=GPIO_Label
PA4.GPIO_Label=MCU_ADC_nCS
PA4.Mode=NSS_Signal_Hard_Output
PA4.Signal=SPI1_NSS
PA7.GPIOParameters=GPIO_Speed_Default_HIGH
PA7.GPIO_Speed_Default_HIGH=GPIO_SPEED_FREQ_VERY_HIGH
PA7.Mode=RMII
PA7.Signal=ETH_CRS_DV
PA8.Mode=I2C
PA8.Signal=I2C3_SCL
PA9.GPIOParameters=GPIO_Label
PA9.GPIO_Label=EEPROM_nWR
PA9.Signal=GPIO_Output
PB11.GPIOParameters=GPIO_Speed_Default_HIGH
PB11.GPIO_Speed_Default_HIGH=GPIO_SPEED_FREQ_VERY_HIGH
PB11.Mode=RMII
PB11.Signal=ETH_TX_EN
PB12.GPIOParameters=GPIO_Speed_Default_HIGH
PB12.GPIO_Speed_Default_HIGH=GPIO_SPEED_FREQ_VERY_HIGH
PB12.Mode=RMII
PB12.Signal=ETH_TXD0
PB13.GPIOParameters=GPIO_Speed_Default_HIGH
PB13.GPIO_Speed_Default_HIGH=GPIO_SPEED_FREQ_VERY_HIGH
PB13.Mode=RMII
PB13.Signal=ETH_TXD1
PB3\ (JTDO/TRACESWO).GPIOParameters=GPIO_Label
PB3\ (JTDO/TRACESWO).GPIO_Label=MCU_ADC_SCLK
PB3\ (JTDO/TRACESWO).Mode=RX_Only_Simplex_Unidirect_Master
PB3\ (JTDO/TRACESWO).Signal=SPI1_SCK
PB4\ (NJTRST).GPIOParameters=GPIO_Label
PB4\ (NJTRST).GPIO_Label=MCU_ADC_SDO
PB4\ (NJTRST).Mode=RX_Only_Simplex_Unidirect_Master
PB4\ (NJTRST).Signal=SPI1_MISO
PB7.GPIOParameters=GPIO_Label
PB7.GPIO_Label=MCU_ADC_SW1
PB7.Signal=GPIO_Output
PB8.GPIOParameters=GPIO_Label
PB8.GPIO_Label=MCU_ADC_SW2
PB8.Signal=GPIO_Output
PB9.GPIOParameters=GPIO_Label
PB9.GPIO_Label=MCU_ADC_SW3
PB9.Signal=GPIO_Output
PC1.GPIOParameters=GPIO_Speed_Default_HIGH
PC1.GPIO_Speed_Default_HIGH=GPIO_SPEED_FREQ_VERY_HIGH
PC1.Mode=RMII
PC1.Signal=ETH_MDC
PC10.GPIOParameters=GPIO_Label
PC10.GPIO_Label=MCU_DAC_SCLK
PC10.Mode=Simplex_Bidirectional_Master
PC10.Signal=SPI3_SCK
PC12.GPIOParameters=GPIO_Label
PC12.GPIO_Label=MCU_DAC_DIN
PC12.Mode=Simplex_Bidirectional_Master
PC12.Signal=SPI3_MOSI
PC4.GPIOParameters=GPIO_Speed_Default_HIGH
PC4.GPIO_Speed_Default_HIGH=GPIO_SPEED_FREQ_VERY_HIGH
PC4.Mode=RMII
PC4.Signal=ETH_RXD0
PC5.GPIOParameters=GPIO_Speed_Default_HIGH
PC5.GPIO_Speed_Default_HIGH=GPIO_SPEED_FREQ_VERY_HIGH
PC5.Mode=RMII
PC5.Signal=ETH_RXD1
PC9.Mode=I2C
PC9.Signal=I2C3_SDA
PD0.GPIOParameters=GPIO_Label
PD0.GPIO_Label=MCU_DAC_nLDAC
PD0.Signal=GPIO_Output
PE0.GPIOParameters=GPIO_Label
PE0.GPIO_Label=MCU_REL_RESET
PE0.Signal=GPIO_Output
PE1.GPIOParameters=GPIO_Label
PE1.GPIO_Label=MCU_REL_SET
PE1.Signal=GPIO_Output
PE2.GPIOParameters=GPIO_Label
PE2.GPIO_Label=MCU_DEF
PE2.Signal=GPIO_Input
PH0-OSC_IN\ (PH0).Mode=HSE-External-Oscillator
PH0-OSC_IN\ (PH0).Signal=RCC_OSC_IN
PH1-OSC_OUT\ (PH1).Mode=HSE-External-Oscillator
PH1-OSC_OUT\ (PH1).Signal=RCC_OSC_OUT
RCC.HSE_VALUE=16000000
RCC.SYSCLKFreq_VALUE=400000000
RCC.SYSCLKSource=RCC_SYSCLKSOURCE_PLLCLK
board=custom

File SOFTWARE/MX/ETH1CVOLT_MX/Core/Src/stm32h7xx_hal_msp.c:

/* USER CODE BEGIN Header */
/**
  ******************************************************************************
  * @file         stm32h7xx_hal_msp.c
  * @brief        This file provides code for the MSP Initialization
  *               and de-Initialization codes.
  ******************************************************************************
  * @attention
  *
  * Copyright (c) 2026 STMicroelectronics.
  * All rights reserved.
  *
  * This software is licensed under terms that can be found in the LICENSE file
  * in the root directory of this software component.
  * If no LICENSE file comes with this software, it is provided AS-IS.
  *
  ******************************************************************************
  */
/* USER CODE END Header */

/* Includes ------------------------------------------------------------------*/
#include "main.h"
/* USER CODE BEGIN Includes */

/* USER CODE END Includes */

/* Private typedef -----------------------------------------------------------*/
/* USER CODE BEGIN TD */

/* USER CODE END TD */

/* Private define ------------------------------------------------------------*/
/* USER CODE BEGIN Define */

/* USER CODE END Define */

/* Private macro -------------------------------------------------------------*/
/* USER CODE BEGIN Macro */

/* USER CODE END Macro */

/* Private variables ---------------------------------------------------------*/
/* USER CODE BEGIN PV */

/* USER CODE END PV */

/* Private function prototypes -----------------------------------------------*/
/* USER CODE BEGIN PFP */

/* USER CODE END PFP */

/* External functions --------------------------------------------------------*/
/* USER CODE BEGIN ExternalFunctions */

/* USER CODE END ExternalFunctions */

/* USER CODE BEGIN 0 */

/* USER CODE END 0 */
/**
  * Initializes the Global MSP.
  */
void HAL_MspInit(void)
{

  /* USER CODE BEGIN MspInit 0 */

  /* USER CODE END MspInit 0 */

  __HAL_RCC_SYSCFG_CLK_ENABLE();

  /* System interrupt init*/
  /* PendSV_IRQn interrupt configuration */
  HAL_NVIC_SetPriority(PendSV_IRQn, 15, 0);

  /* USER CODE BEGIN MspInit 1 */

  /* USER CODE END MspInit 1 */
}

/**
  * @brief I2C MSP Initialization
  * This function configures the hardware resources used in this example
  * @param hi2c: I2C handle pointer
  * @retval None
  */
void HAL_I2C_MspInit(I2C_HandleTypeDef* hi2c)
{
  GPIO_InitTypeDef GPIO_InitStruct = {0};
  if(hi2c->Instance==I2C1)
  {
    /* USER CODE BEGIN I2C1_MspInit 0 */

    /* USER CODE END I2C1_MspInit 0 */
    LL_RCC_SetI2CClockSource(LL_RCC_I2C123_CLKSOURCE_PCLK1);

    __HAL_RCC_GPIOB_CLK_ENABLE();
    /**I2C1 GPIO Configuration
    PB6     ------> I2C1_SCL
    PB7     ------> I2C1_SDA
    */
    GPIO_InitStruct.Pin = GPIO_PIN_6|GPIO_PIN_7;
    GPIO_InitStruct.Mode = GPIO_MODE_AF_OD;
    GPIO_InitStruct.Pull = GPIO_NOPULL;
    GPIO_InitStruct.Speed = GPIO_SPEED_FREQ_LOW;
    GPIO_InitStruct.Alternate = GPIO_AF4_I2C1;
    HAL_GPIO_Init(GPIOB, &GPIO_InitStruct);

    /* Peripheral clock enable */
    __HAL_RCC_I2C1_CLK_ENABLE();
    /* USER CODE BEGIN I2C1_MspInit 1 */

    /* USER CODE END I2C1_MspInit 1 */

  }

}

/**
  * @brief I2C MSP De-Initialization
  * This function freeze the hardware resources used in this example
  * @param hi2c: I2C handle pointer
  * @retval None
  */
void HAL_I2C_MspDeInit(I2C_HandleTypeDef* hi2c)
{
  if(hi2c->Instance==I2C1)
  {
    /* USER CODE BEGIN I2C1_MspDeInit 0 */

    /* USER CODE END I2C1_MspDeInit 0 */
    /* Peripheral clock disable */
    __HAL_RCC_I2C1_CLK_DISABLE();

    /**I2C1 GPIO Configuration
    PB6     ------> I2C1_SCL
    PB7     ------> I2C1_SDA
    */
    HAL_GPIO_DeInit(GPIOB, GPIO_PIN_6);

    HAL_GPIO_DeInit(GPIOB, GPIO_PIN_7);

    /* USER CODE BEGIN I2C1_MspDeInit 1 */

    /* USER CODE END I2C1_MspDeInit 1 */
  }

}

/**
  * @brief SPI MSP Initialization
  * This function configures the hardware resources used in this example
  * @param hspi: SPI handle pointer
  * @retval None
  */
void HAL_SPI_MspInit(SPI_HandleTypeDef* hspi)
{
  GPIO_InitTypeDef GPIO_InitStruct = {0};
  if(hspi->Instance==SPI3)
  {
    /* USER CODE BEGIN SPI3_MspInit 0 */

    /* USER CODE END SPI3_MspInit 0 */
    LL_RCC_SetSPIClockSource(LL_RCC_SPI123_CLKSOURCE_PLL1Q);

    /* Peripheral clock enable */
    __HAL_RCC_SPI3_CLK_ENABLE();

    __HAL_RCC_GPIOA_CLK_ENABLE();
    __HAL_RCC_GPIOC_CLK_ENABLE();
    /**SPI3 GPIO Configuration
    PA15 (JTDI)     ------> SPI3_NSS
    PC10     ------> SPI3_SCK
    PC11     ------> SPI3_MISO
    PC12     ------> SPI3_MOSI
    */
    GPIO_InitStruct.Pin = GPIO_PIN_15;
    GPIO_InitStruct.Mode = GPIO_MODE_AF_PP;
    GPIO_InitStruct.Pull = GPIO_NOPULL;
    GPIO_InitStruct.Speed = GPIO_SPEED_FREQ_LOW;
    GPIO_InitStruct.Alternate = GPIO_AF6_SPI3;
    HAL_GPIO_Init(GPIOA, &GPIO_InitStruct);

    GPIO_InitStruct.Pin = GPIO_PIN_10|GPIO_PIN_11|GPIO_PIN_12;
    GPIO_InitStruct.Mode = GPIO_MODE_AF_PP;
    GPIO_InitStruct.Pull = GPIO_NOPULL;
    GPIO_InitStruct.Speed = GPIO_SPEED_FREQ_LOW;
    GPIO_InitStruct.Alternate = GPIO_AF6_SPI3;
    HAL_GPIO_Init(GPIOC, &GPIO_InitStruct);

    /* USER CODE BEGIN SPI3_MspInit 1 */

    /* USER CODE END SPI3_MspInit 1 */
  }
  else if(hspi->Instance==SPI4)
  {
    /* USER CODE BEGIN SPI4_MspInit 0 */

    /* USER CODE END SPI4_MspInit 0 */

    LL_RCC_SetSPIClockSource(LL_RCC_SPI45_CLKSOURCE_PCLK2);

    /* Peripheral clock enable */
    __HAL_RCC_SPI4_CLK_ENABLE();

    __HAL_RCC_GPIOE_CLK_ENABLE();
    /**SPI4 GPIO Configuration
    PE2     ------> SPI4_SCK
    PE4     ------> SPI4_NSS
    PE5     ------> SPI4_MISO
    PE6     ------> SPI4_MOSI
    */
    GPIO_InitStruct.Pin = GPIO_PIN_2|GPIO_PIN_4|GPIO_PIN_5|GPIO_PIN_6;
    GPIO_InitStruct.Mode = GPIO_MODE_AF_PP;
    GPIO_InitStruct.Pull = GPIO_NOPULL;
    GPIO_InitStruct.Speed = GPIO_SPEED_FREQ_LOW;
    GPIO_InitStruct.Alternate = GPIO_AF5_SPI4;
    HAL_GPIO_Init(GPIOE, &GPIO_InitStruct);

    /* USER CODE BEGIN SPI4_MspInit 1 */

    /* USER CODE END SPI4_MspInit 1 */
  }
  else if(hspi->Instance==SPI6)
  {
    /* USER CODE BEGIN SPI6_MspInit 0 */

    /* USER CODE END SPI6_MspInit 0 */

    LL_RCC_SetSPIClockSource(LL_RCC_SPI6_CLKSOURCE_PCLK4);

    /* Peripheral clock enable */
    __HAL_RCC_SPI6_CLK_ENABLE();

    __HAL_RCC_GPIOA_CLK_ENABLE();
    /**SPI6 GPIO Configuration
    PA4     ------> SPI6_NSS
    PA5     ------> SPI6_SCK
    PA6     ------> SPI6_MISO
    */
    GPIO_InitStruct.Pin = GPIO_PIN_4|GPIO_PIN_5|GPIO_PIN_6;
    GPIO_InitStruct.Mode = GPIO_MODE_AF_PP;
    GPIO_InitStruct.Pull = GPIO_NOPULL;
    GPIO_InitStruct.Speed = GPIO_SPEED_FREQ_LOW;
    GPIO_InitStruct.Alternate = GPIO_AF8_SPI6;
    HAL_GPIO_Init(GPIOA, &GPIO_InitStruct);

    /* USER CODE BEGIN SPI6_MspInit 1 */

    /* USER CODE END SPI6_MspInit 1 */
  }

}

/**
  * @brief SPI MSP De-Initialization
  * This function freeze the hardware resources used in this example
  * @param hspi: SPI handle pointer
  * @retval None
  */
void HAL_SPI_MspDeInit(SPI_HandleTypeDef* hspi)
{
  if(hspi->Instance==SPI3)
  {
    /* USER CODE BEGIN SPI3_MspDeInit 0 */

    /* USER CODE END SPI3_MspDeInit 0 */
    /* Peripheral clock disable */
    __HAL_RCC_SPI3_CLK_DISABLE();

    /**SPI3 GPIO Configuration
    PA15 (JTDI)     ------> SPI3_NSS
    PC10     ------> SPI3_SCK
    PC11     ------> SPI3_MISO
    PC12     ------> SPI3_MOSI
    */
    HAL_GPIO_DeInit(GPIOA, GPIO_PIN_15);

    HAL_GPIO_DeInit(GPIOC, GPIO_PIN_10|GPIO_PIN_11|GPIO_PIN_12);

    /* USER CODE BEGIN SPI3_MspDeInit 1 */

    /* USER CODE END SPI3_MspDeInit 1 */
  }
  else if(hspi->Instance==SPI4)
  {
    /* USER CODE BEGIN SPI4_MspDeInit 0 */

    /* USER CODE END SPI4_MspDeInit 0 */
    /* Peripheral clock disable */
    __HAL_RCC_SPI4_CLK_DISABLE();

    /**SPI4 GPIO Configuration
    PE2     ------> SPI4_SCK
    PE4     ------> SPI4_NSS
    PE5     ------> SPI4_MISO
    PE6     ------> SPI4_MOSI
    */
    HAL_GPIO_DeInit(GPIOE, GPIO_PIN_2|GPIO_PIN_4|GPIO_PIN_5|GPIO_PIN_6);

    /* USER CODE BEGIN SPI4_MspDeInit 1 */

    /* USER CODE END SPI4_MspDeInit 1 */
  }
  else if(hspi->Instance==SPI6)
  {
    /* USER CODE BEGIN SPI6_MspDeInit 0 */

    /* USER CODE END SPI6_MspDeInit 0 */
    /* Peripheral clock disable */
    __HAL_RCC_SPI6_CLK_DISABLE();

    /**SPI6 GPIO Configuration
    PA4     ------> SPI6_NSS
    PA5     ------> SPI6_SCK
    PA6     ------> SPI6_MISO
    */
    HAL_GPIO_DeInit(GPIOA, GPIO_PIN_4|GPIO_PIN_5|GPIO_PIN_6);

    /* USER CODE BEGIN SPI6_MspDeInit 1 */

    /* USER CODE END SPI6_MspDeInit 1 */
  }

}

/* USER CODE BEGIN 1 */

/* USER CODE END 1 */

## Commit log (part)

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2026-02-14 Development
2026-02-27 Hardware development
